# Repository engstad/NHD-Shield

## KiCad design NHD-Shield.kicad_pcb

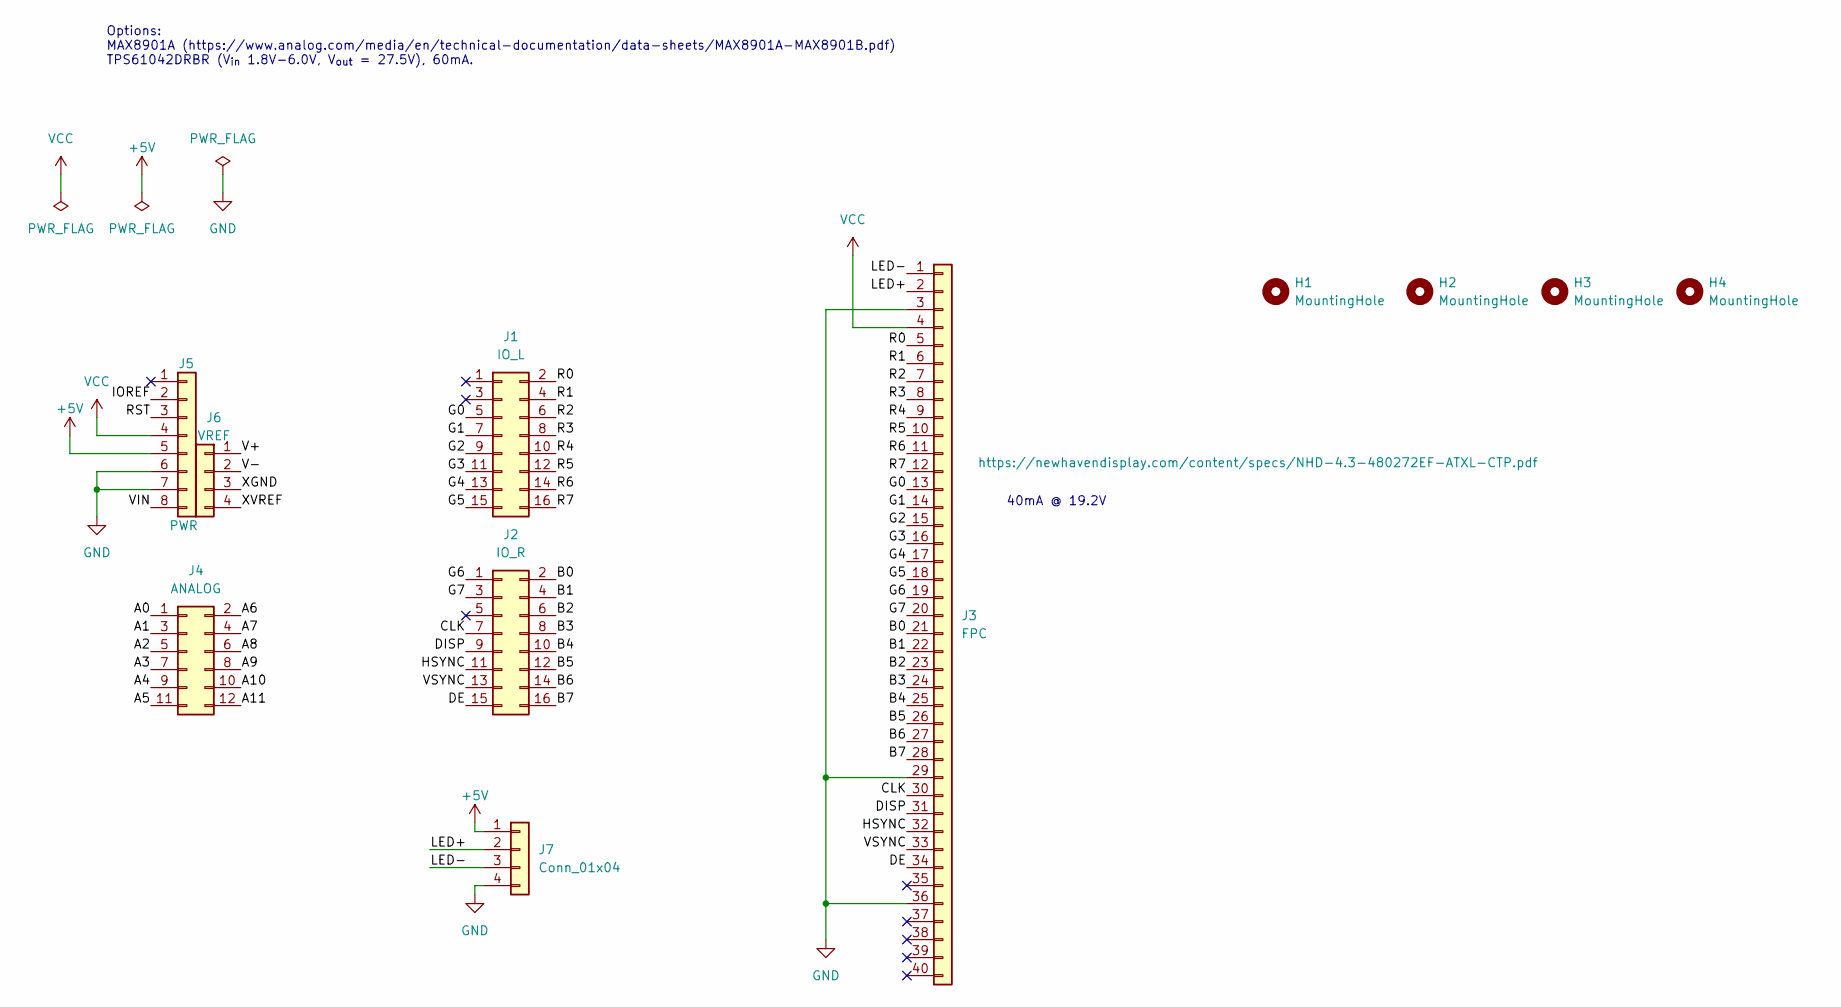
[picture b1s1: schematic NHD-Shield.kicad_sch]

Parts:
H1, H2, H3, H4: MountingHole; MountingHole_3.5mm
J1: IO_L; PinHeader_2x08_P2.54mm_Vertical
J2: IO_R; PinHeader_2x08_P2.54mm_Vertical
J3: FPC; Molex_FPC_51296-4094_40Pin_0.5mm
J4: ANALOG; PinHeader_2x06_P2.54mm_Vertical
J5: PWR; PinHeader_1x08_P2.54mm_Vertical
J6: VREF; PinHeader_1x04_P2.54mm_Vertical
J7: Conn_01x04; PinHeader_1x04_P2.54mm_Horizontal

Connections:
+5V: J5.5, J7.1
/A0: J4.1
/A1: J4.3
/A2: J4.5
/A3: J4.7
/A4: J4.9
/A5: J4.11
/A6: J4.2
/A7: J4.4
/A8: J4.6
/A9: J4.8
/A10: J4.10
/A11: J4.12
/B0: J2.2, J3.21
/B1: J2.4, J3.22
/B2: J2.6, J3.23
/B3: J2.8, J3.24
/B4: J2.10, J3.25
/B5: J2.12, J3.26
/B6: J2.14, J3.27
/B7: J2.16, J3.28
/CLK: J2.7, J3.30
/DE: J2.15, J3.34
/DISP: J2.9, J3.31
/G0: J1.5, J3.13
/G1: J1.7, J3.14
/G2: J1.9, J3.15
/G3: J1.11, J3.16
/G4: J1.13, J3.17
/G5: J1.15, J3.18
/G6: J2.1, J3.19
/G7: J2.3, J3.20
/HSYNC: J2.11, J3.32
/IOREF: J5.2
/LED+: J3.2, J7.2
/LED-: J3.1, J7.3
/R0: J1.2, J3.5
/R1: J1.4, J3.6
/R2: J1.6, J3.7
/R3: J1.8, J3.8
/R4: J1.10, J3.9
/R5: J1.12, J3.10
/R6: J1.14, J3.11
/R7: J1.16, J3.12
/RST: J5.3
/V+: J6.1
/V-: J6.2
/VIN: J5.8
/VSYNC: J2.13, J3.33
/XGND: J6.3
/XVREF: J6.4
GND: J3.3, J3.29, J3.36, J5.6, J5.7, J7.4
VCC: J3.4, J5.4

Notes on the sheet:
Options: MAX8901A (https://www.analog.com/media/en/technical-documentation/data-sheets/MAX8901A-MAX8901B.pdf) TPS61042DRBR (V_{in} 1.8V-6.0V, V_{out} = 27.5V), 60mA.
40mA @ 19.2V

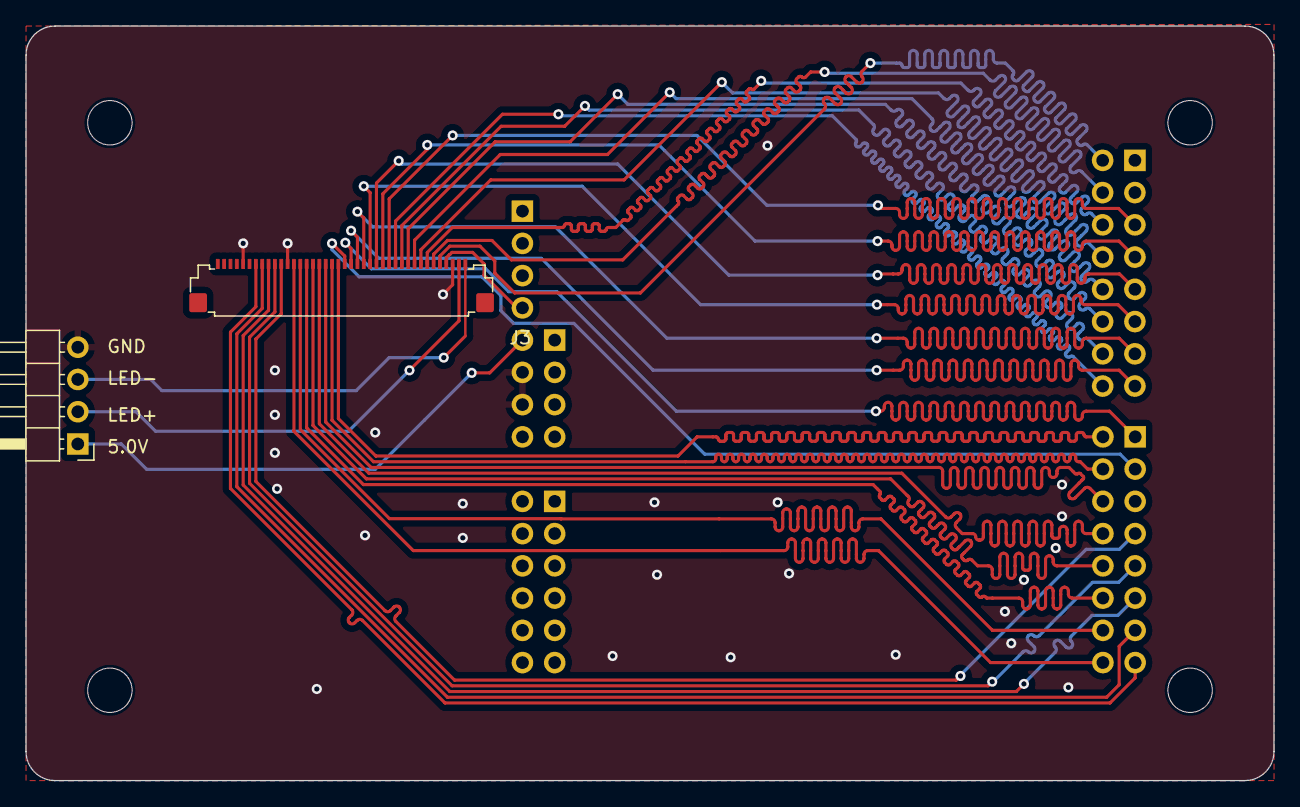
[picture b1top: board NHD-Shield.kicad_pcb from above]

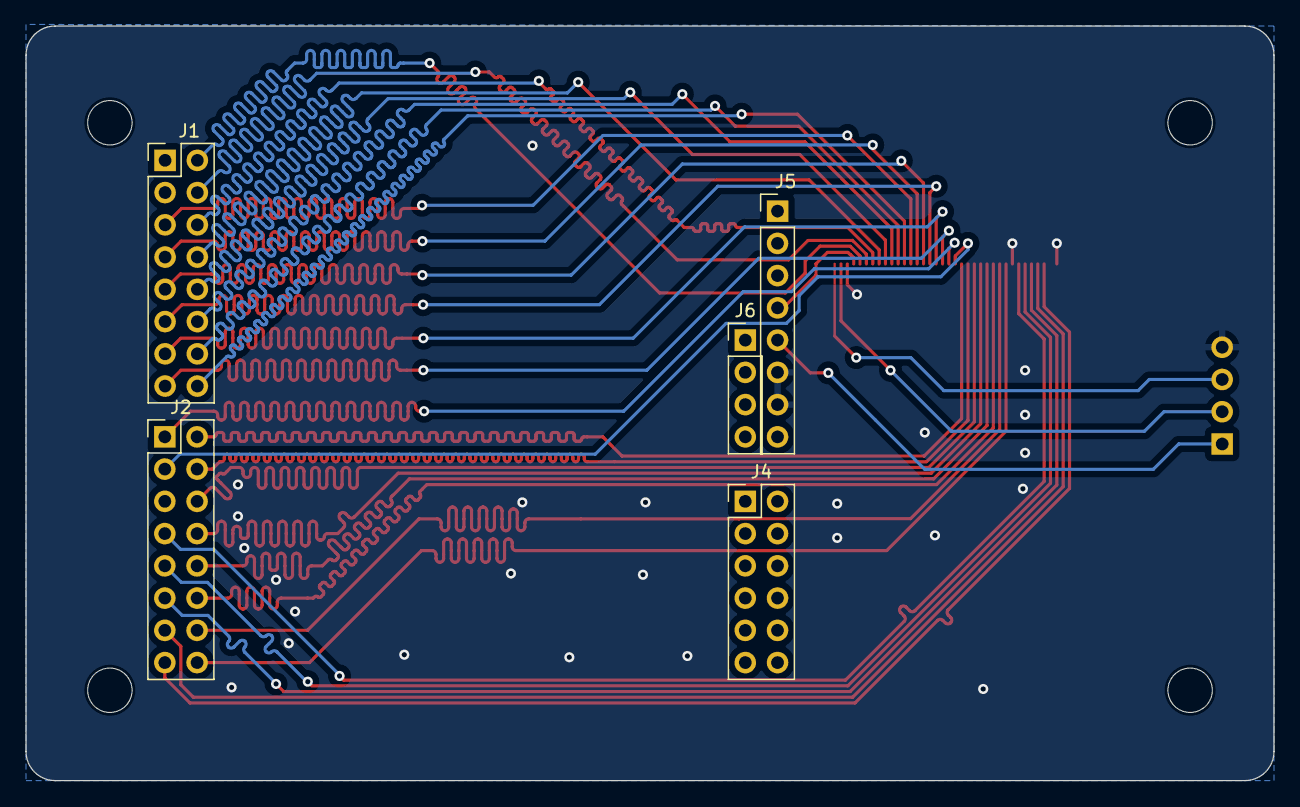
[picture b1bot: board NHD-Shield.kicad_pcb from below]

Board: 2 copper layers, 98.3 x 59.4 mm, 11 parts (5 on the bottom side), 34 nets.

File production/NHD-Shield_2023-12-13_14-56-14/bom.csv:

Designator,Footprint,Quantity,Value,LCSC Part #
"H1, H2, H3, H4",MountingHole_3.5mm,4,MountingHole,
J1,PinHeader_2x08_P2.54mm_Vertical,1,IO_L,
J2,PinHeader_2x08_P2.54mm_Vertical,1,IO_R,
J3,Molex_FPC_51296-4094_40Pin_0.5mm,1,FPC,
J4,PinHeader_2x06_P2.54mm_Vertical,1,ANALOG,
J5,PinHeader_1x08_P2.54mm_Vertical,1,PWR,
J6,PinHeader_1x04_P2.54mm_Vertical,1,VREF,
J7,PinHeader_1x04_P2.54mm_Horizontal,1,Conn_01x04,

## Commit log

2024-01-12 Initial commit.
